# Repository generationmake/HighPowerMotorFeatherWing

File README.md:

# HighPowerMotorFeatherWing
HighPowerMotorFeatherWing with Infineon IFX007T drivers for two DC motors, up to 40V and 55A, compatible to Adafruit Feather

## PCB

### Top

### Bottom

## License

This hardware is licensed under the CERN OHL v. 1.2

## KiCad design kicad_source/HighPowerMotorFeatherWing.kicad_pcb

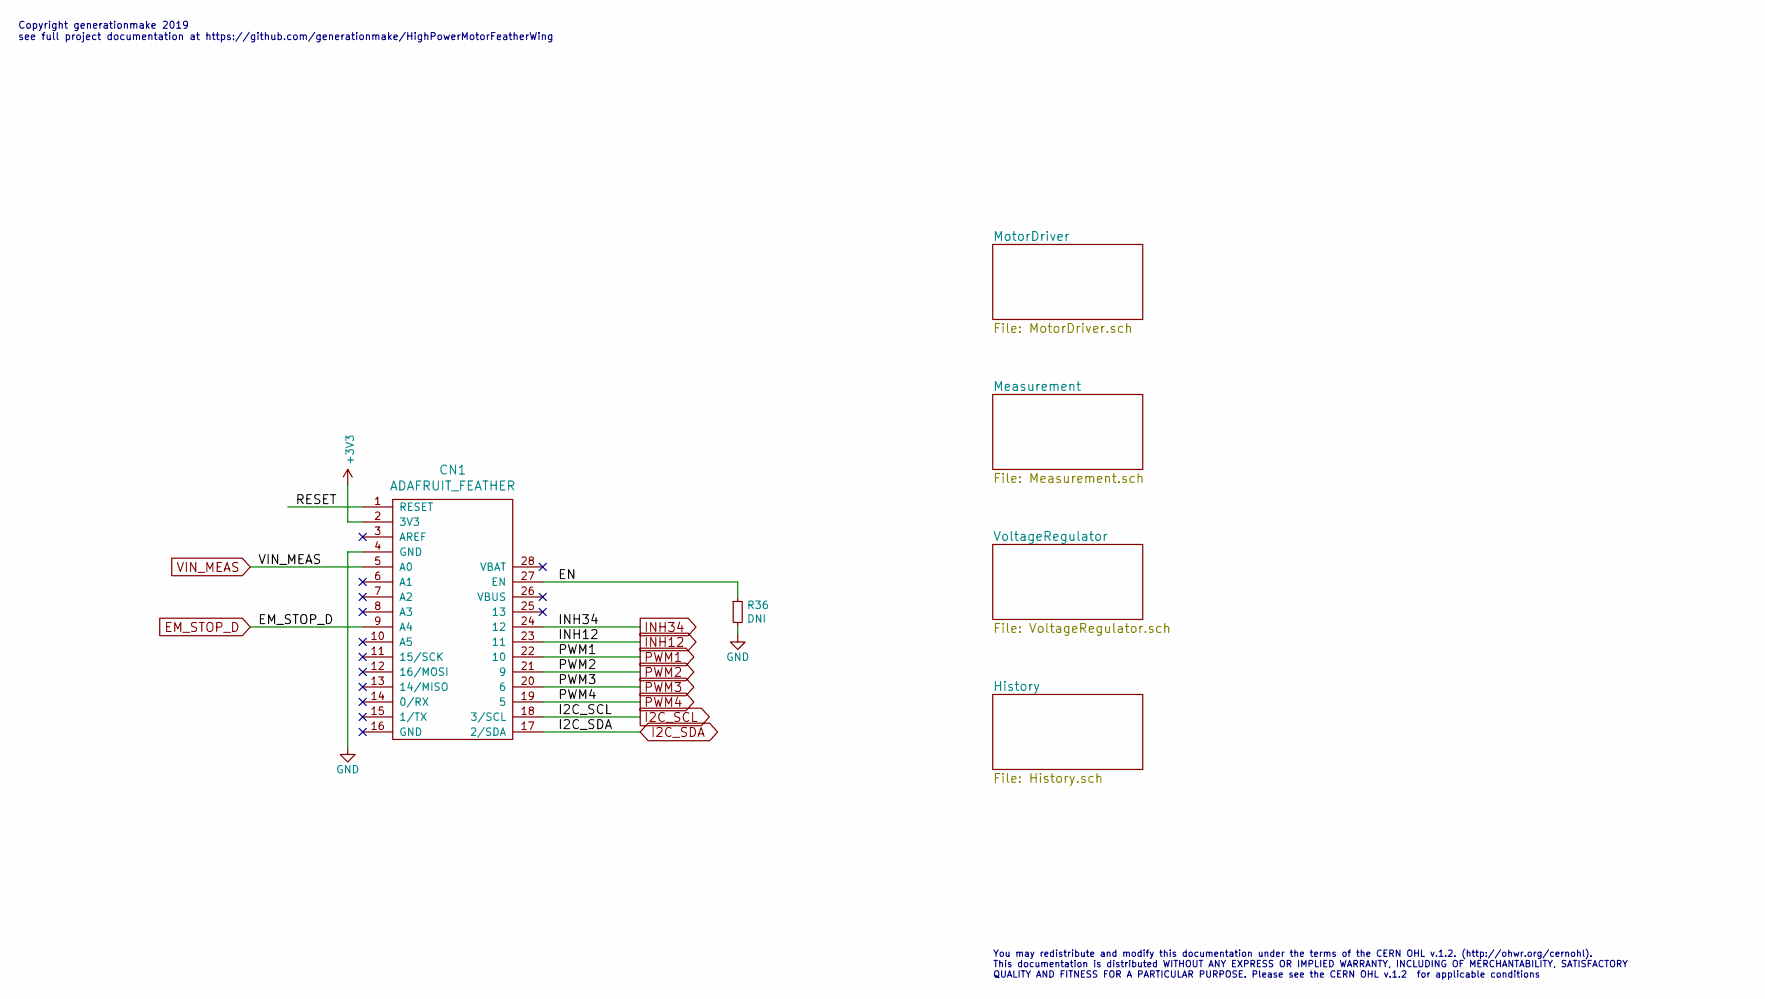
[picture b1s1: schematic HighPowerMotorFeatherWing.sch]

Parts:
CN1: ADAFRUIT_FEATHER; ADAFRUIT_FEATHER_HOLES
R36: DNI; R_0603

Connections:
+3V3: CN1.2 (3V3); also elsewhere on the board
/EN: CN1.27 (EN), R36.1
EM_STOP_D: CN1.9 (A4); also elsewhere on the board
GND: CN1.4 (GND), R36.2; also elsewhere on the board
I2C_SCL: CN1.18 (3/SCL); also elsewhere on the board
I2C_SDA: CN1.17 (2/SDA); also elsewhere on the board
INH12: CN1.23 (11); also elsewhere on the board
INH34: CN1.24 (12); also elsewhere on the board
PWM1: CN1.22 (10); also elsewhere on the board
PWM2: CN1.21 (9); also elsewhere on the board
PWM3: CN1.20 (6); also elsewhere on the board
PWM4: CN1.19 (5); also elsewhere on the board
VIN_MEAS: CN1.5 (A0); also elsewhere on the board

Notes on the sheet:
Copyright generationmake 2019 see full project documentation at https://github.com/generationmake/HighPowerMotorFeatherWing
You may redistribute and modify this documentation under the terms of the CERN OHL v.1.2. (http://ohwr.org/cernohl). This documentation is distributed WITHOUT ANY EXPRESS OR IMPLIED WARRANTY, INCLUDING OF MERCHANTABILITY, SATISFACTORY QUALITY AND FITNESS FOR A PARTICULAR PURPOSE. Please see the CER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

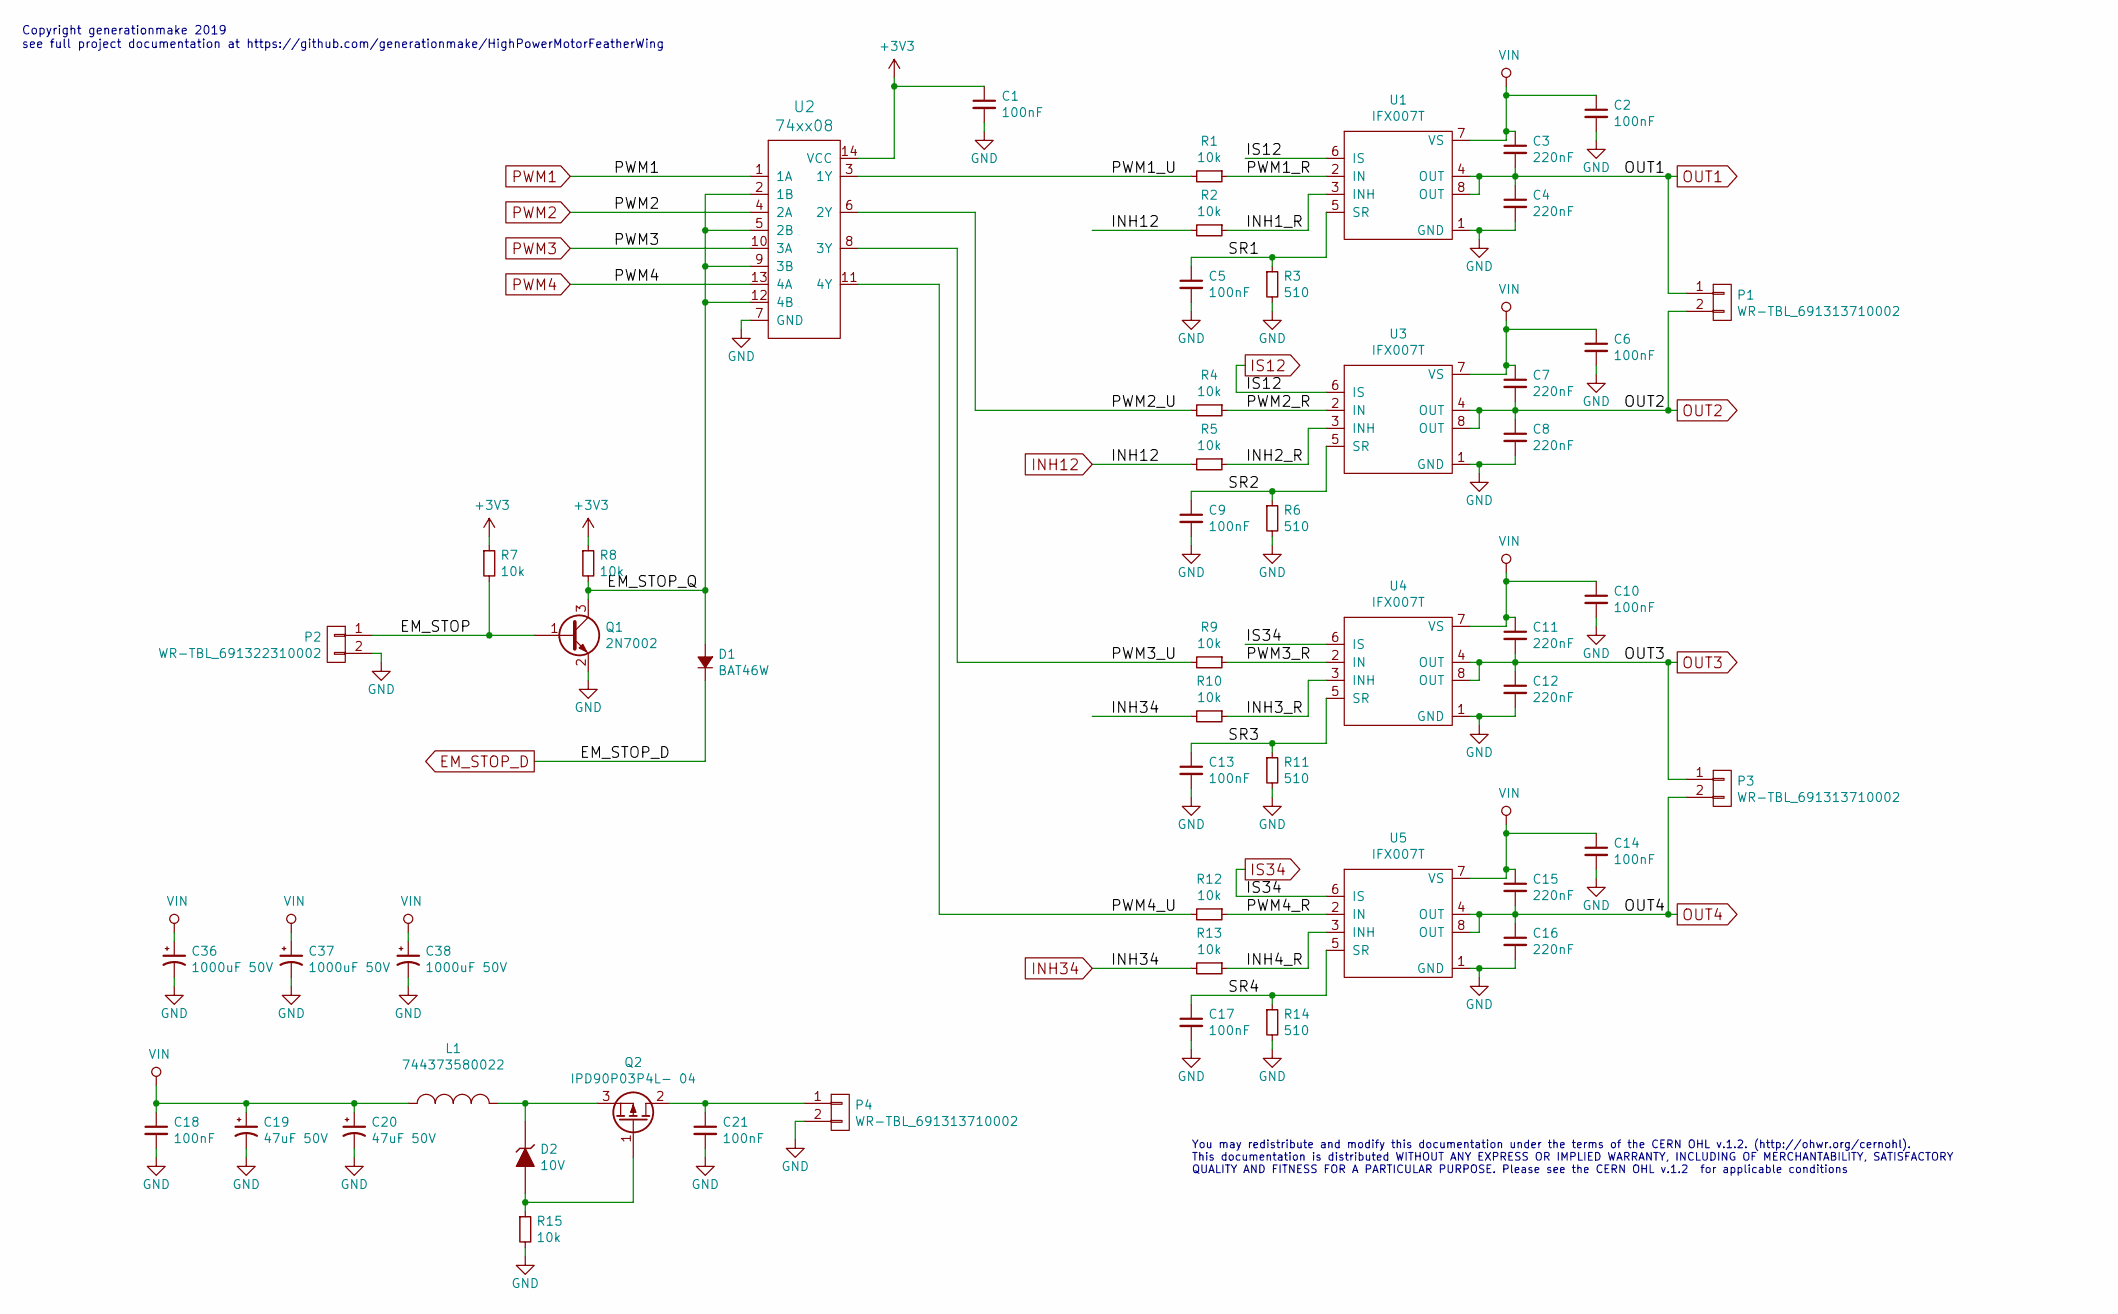
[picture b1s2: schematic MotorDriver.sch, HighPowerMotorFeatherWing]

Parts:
C1, C2, C5, C6, C9, C10, C13, C14, C17, C18, C21: 100nF; C_0603
C3, C4, C7, C8, C11, C12, C15, C16: 220nF; C_0603
C19, C20: 47uF 50V; TantalC_SizeD_EIA-7343_Wave
C36, C37, C38: 1000uF 50V; C_elec_THT_16x25_RM7.5
D1: BAT46W; SOD-123
D2: 10V; SOD-123
L1: 744373580022; WE-LHMI80xx
P1, P3, P4: WR-TBL_691313710002
P2: WR-TBL_691322310002
Q1: 2N7002; SOT-23
Q2: IPD90P03P4L- 04; TO-252-2Lead
R1, R2, R4, R5, R7, R8, R9, R10, R12, R13, R15: 10k; R_0603
R3, R6, R11, R14: 510; R_0603
U1, U3, U4, U5: IFX007T; TO-263-7Lead
U2: 74xx08; SOIC-14_3.9x8.7mm_Pitch1.27mm

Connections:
+3V3: C1.1, R7.1, R8.1, U2.14 (VCC); also elsewhere on the board
/MotorDriver/EM_STOP: P2.1, Q1.1 (B), R7.2
/MotorDriver/EM_STOP_Q: D1.2 (A), Q1.3 (C), R8.2, U2.2 (1B), U2.5 (2B), U2.9 (3B), U2.12 (4B)
/MotorDriver/INH1_R: R2.1, U1.3 (INH)
/MotorDriver/INH2_R: R5.1, U3.3 (INH)
/MotorDriver/INH3_R: R10.1, U4.3 (INH)
/MotorDriver/INH4_R: R13.1, U5.3 (INH)
/MotorDriver/PWM1_R: R1.1, U1.2 (IN)
/MotorDriver/PWM1_U: R1.2, U2.3 (1Y)
/MotorDriver/PWM2_R: R4.1, U3.2 (IN)
/MotorDriver/PWM2_U: R4.2, U2.6 (2Y)
/MotorDriver/PWM3_R: R9.1, U4.2 (IN)
/MotorDriver/PWM3_U: R9.2, U2.8 (3Y)
/MotorDriver/PWM4_R: R12.1, U5.2 (IN)
/MotorDriver/PWM4_U: R12.2, U2.11 (4Y)
/MotorDriver/SR1: C5.1, R3.1, U1.5 (SR)
/MotorDriver/SR2: C9.1, R6.1, U3.5 (SR)
/MotorDriver/SR3: C13.1, R11.1, U4.5 (SR)
/MotorDriver/SR4: C17.1, R14.1, U5.5 (SR)
EM_STOP_D: D1.1 (K); also elsewhere on the board
GND: C1.2, C2.2, C4.2, C5.2, C6.2, C8.2, C9.2, C10.2, C12.2, C13.2, C14.2, C16.2, C17.2, C18.2, C19.2, C20.2, C21.2, C36.2, C37.2, C38.2, P2.2, P4.2, Q1.2 (E), R3.2, R6.2, R11.2, R14.2, R15.2, U1.1 (GND), U2.7 (GND), U3.1 (GND), U4.1 (GND), U5.1 (GND); also elsewhere on the board
INH12: R2.2, R5.2; also elsewhere on the board
INH34: R10.2, R13.2; also elsewhere on the board
IS12: U1.6 (IS), U3.6 (IS); also elsewhere on the board
IS34: U4.6 (IS), U5.6 (IS); also elsewhere on the board
unnamed: C21.1, P4.1, Q2.2 (D)
unnamed: D2.1 (K), L1.2, Q2.3 (S)
unnamed: D2.2 (A), Q2.1 (G), R15.1
OUT1: C3.2, C4.1, P1.1, U1.4 (OUT), U1.8 (OUT); also elsewhere on the board
OUT2: C7.2, C8.1, P1.2, U3.4 (OUT), U3.8 (OUT); also elsewhere on the board
OUT3: C11.2, C12.1, P3.1, U4.4 (OUT), U4.8 (OUT); also elsewhere on the board
OUT4: C15.2, C16.1, P3.2, U5.4 (OUT), U5.8 (OUT); also elsewhere on the board
PWM1: U2.1 (1A); also elsewhere on the board
PWM2: U2.4 (2A); also elsewhere on the board
PWM3: U2.10 (3A); also elsewhere on the board
PWM4: U2.13 (4A); also elsewhere on the board
VIN: C2.1, C3.1, C6.1, C7.1, C10.1, C11.1, C14.1, C15.1, C18.1, C19.1, C20.1, C36.1, C37.1, C38.1, L1.1, U1.7 (VS), U3.7 (VS), U4.7 (VS), U5.7 (VS); also elsewhere on the board

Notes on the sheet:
Copyright generationmake 2019 see full project documentation at https://github.com/generationmake/HighPowerMotorFeatherWing
You may redistribute and modify this documentation under the terms of the CERN OHL v.1.2. (http://ohwr.org/cernohl). This documentation is distributed WITHOUT ANY EXPRESS OR IMPLIED WARRANTY, INCLUDING OF MERCHANTABILITY, SATISFACTORY QUALITY AND FITNESS FOR A PARTICULAR PURPOSE. Please see the CER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

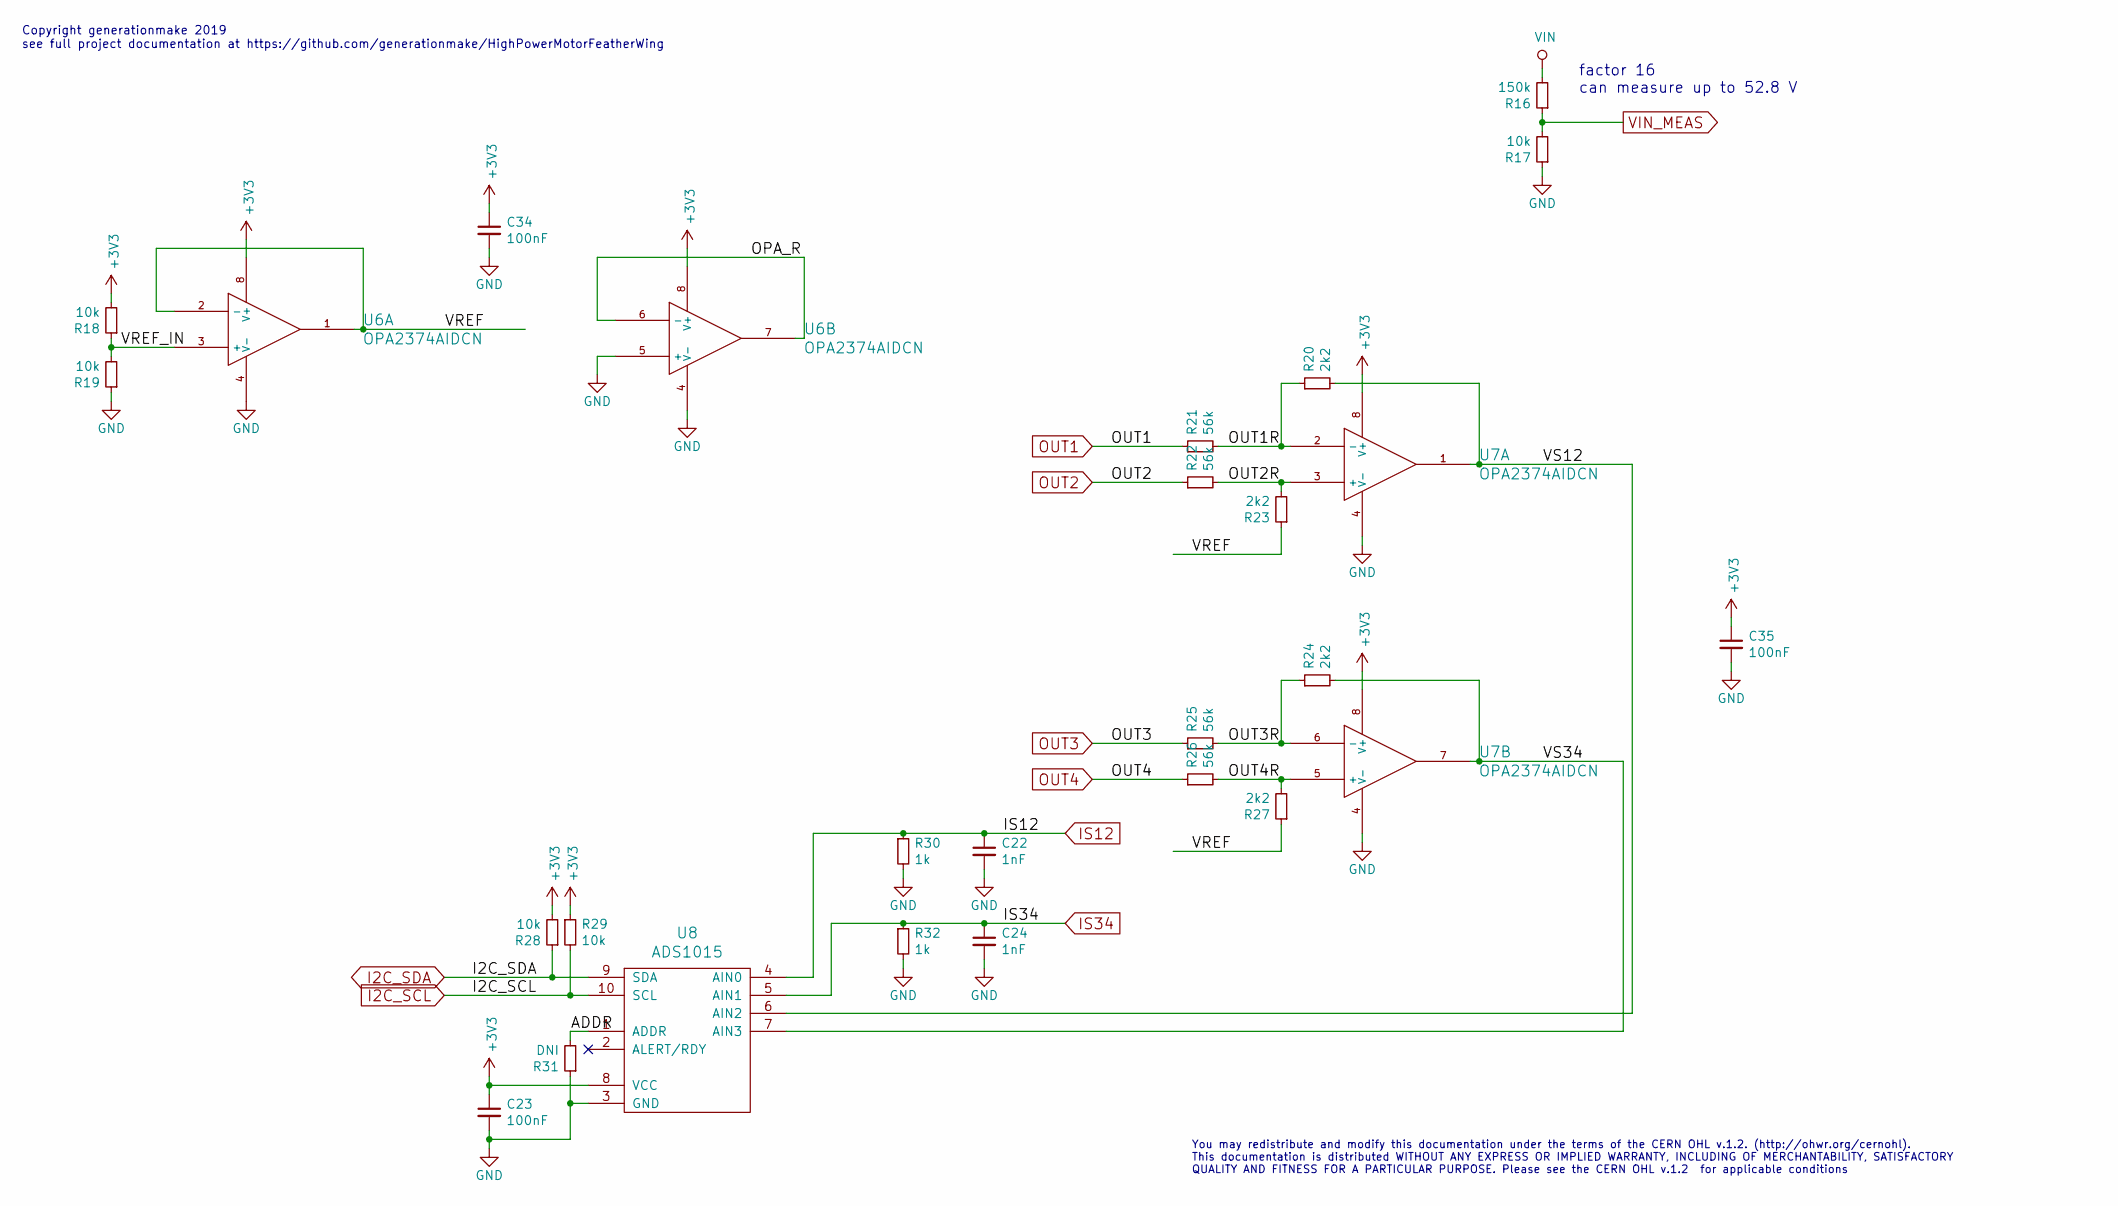
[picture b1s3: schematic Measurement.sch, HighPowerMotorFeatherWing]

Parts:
C22, C24: 1nF; C_0603
C23, C34, C35: 100nF; C_0603
R16: 150k; R_0603
R17, R18, R19, R28, R29: 10k; R_0603
R20, R23, R24, R27: 2k2; R_0603
R21, R22, R25, R26: 56k; R_0603
R30, R32: 1k; R_0603
R31: DNI; R_0603
U6, U7: OPA2374AIDCN; SOIC-8_3.9x4.9mm_Pitch1.27mm
U8: ADS1015; MSOP-10_3x3mm_Pitch0.5mm

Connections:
+3V3: C23.1, C34.1, C35.1, R18.2, R28.2, R29.1, U6.8 (V+), U7.8 (V+), U8.8 (VCC); also elsewhere on the board
/Measurement/ADDR: R31.2, U8.1 (ADDR)
/Measurement/OPA_R: U6.6 (-), U6.7
/Measurement/OUT1R: R20.1, R21.2, U7.2 (-)
/Measurement/OUT2R: R22.2, R23.2, U7.3 (+)
/Measurement/OUT3R: R24.1, R25.2, U7.6 (-)
/Measurement/OUT4R: R26.2, R27.2, U7.5 (+)
/Measurement/VREF: R23.1, R27.1, U6.1, U6.2 (-)
/Measurement/VREF_IN: R18.1, R19.2, U6.3 (+)
/Measurement/VS12: R20.2, U7.1, U8.6 (AIN2)
/Measurement/VS34: R24.2, U7.7, U8.7 (AIN3)
GND: C22.2, C23.2, C24.2, C34.2, C35.2, R17.1, R19.1, R30.2, R31.1, R32.2, U6.4 (V-), U6.5 (+), U7.4 (V-), U8.3 (GND); also elsewhere on the board
I2C_SCL: R29.2, U8.10 (SCL); also elsewhere on the board
I2C_SDA: R28.1, U8.9 (SDA); also elsewhere on the board
IS12: C22.1, R30.1, U8.4 (AIN0); also elsewhere on the board
IS34: C24.1, R32.1, U8.5 (AIN1); also elsewhere on the board
OUT1: R21.1; also elsewhere on the board
OUT2: R22.1; also elsewhere on the board
OUT3: R25.1; also elsewhere on the board
OUT4: R26.1; also elsewhere on the board
VIN: R16.2; also elsewhere on the board
VIN_MEAS: R16.1, R17.2; also elsewhere on the board

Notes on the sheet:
Copyright generationmake 2019 see full project documentation at https://github.com/generationmake/HighPowerMotorFeatherWing
You may redistribute and modify this documentation under the terms of the CERN OHL v.1.2. (http://ohwr.org/cernohl). This documentation is distributed WITHOUT ANY EXPRESS OR IMPLIED WARRANTY, INCLUDING OF MERCHANTABILITY, SATISFACTORY QUALITY AND FITNESS FOR A PARTICULAR PURPOSE. Please see the CER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
factor 16 can measure up to 52.8 V

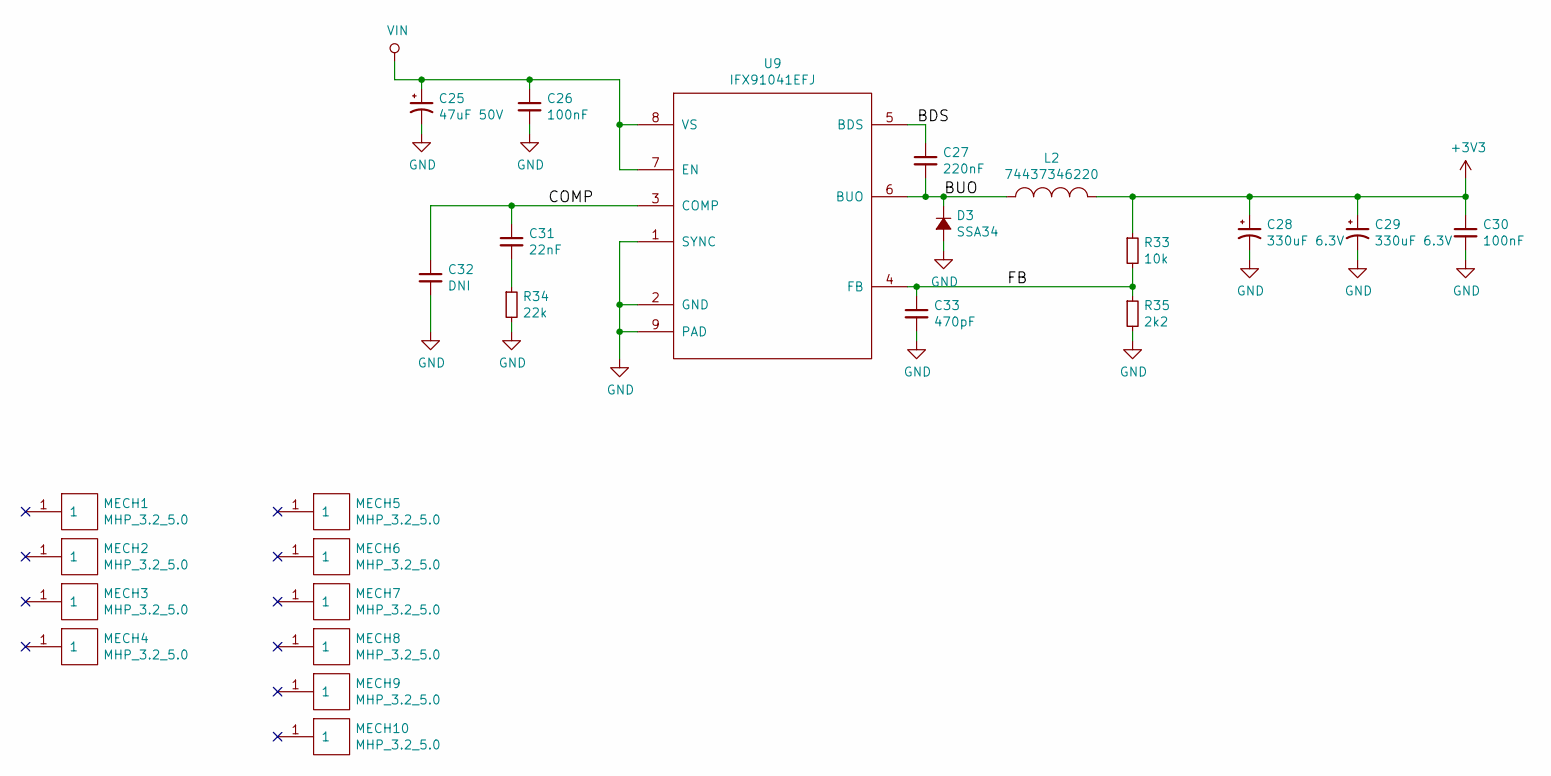
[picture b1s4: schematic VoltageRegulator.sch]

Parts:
C25: 47uF 50V; TantalC_SizeD_EIA-7343_Wave
C26, C30: 100nF; C_0603
C27: 220nF; C_0603
C28, C29: 330uF 6.3V; TantalC_SizeD_EIA-7343_Wave
C31: 22nF; C_0603
C32: DNI; C_0603
C33: 470pF; C_0603
D3: SSA34; SMA_Standard
L2: 74437346220; WE-LHMI70xx
MECH1, MECH2, MECH3, MECH4, MECH5, MECH6, MECH7, MECH8, MECH9, MECH10: MHP_3.2_5.0
R33: 10k; R_0603
R34: 22k; R_0603
R35: 2k2; R_0603
U9: IFX91041EFJ; SOIC-8-1EP_3.9x4.9mm_Pitch1.27mm

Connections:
+3V3: C28.1, C29.1, C30.1, L2.2, R33.1; also elsewhere on the board
/VoltageRegulator/BDS: C27.1, U9.5 (BDS)
/VoltageRegulator/BUO: C27.2, D3.1 (K), L2.1, U9.6 (BUO)
/VoltageRegulator/COMP: C31.1, C32.1, U9.3 (COMP)
/VoltageRegulator/FB: C33.1, R33.2, R35.1, U9.4 (FB)
GND: C25.2, C26.2, C28.2, C29.2, C30.2, C32.2, C33.2, D3.2 (A), R34.2, R35.2, U9.1 (SYNC), U9.2 (GND), U9.9 (PAD); also elsewhere on the board
unnamed: C31.2, R34.1
VIN: C25.1, C26.1, U9.7 (EN), U9.8 (VS); also elsewhere on the board

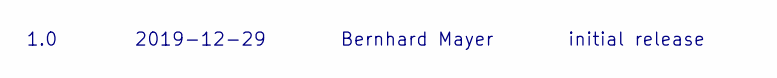
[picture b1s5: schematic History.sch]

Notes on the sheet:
1.0
2019-12-29
Bernhard Mayer
initial release

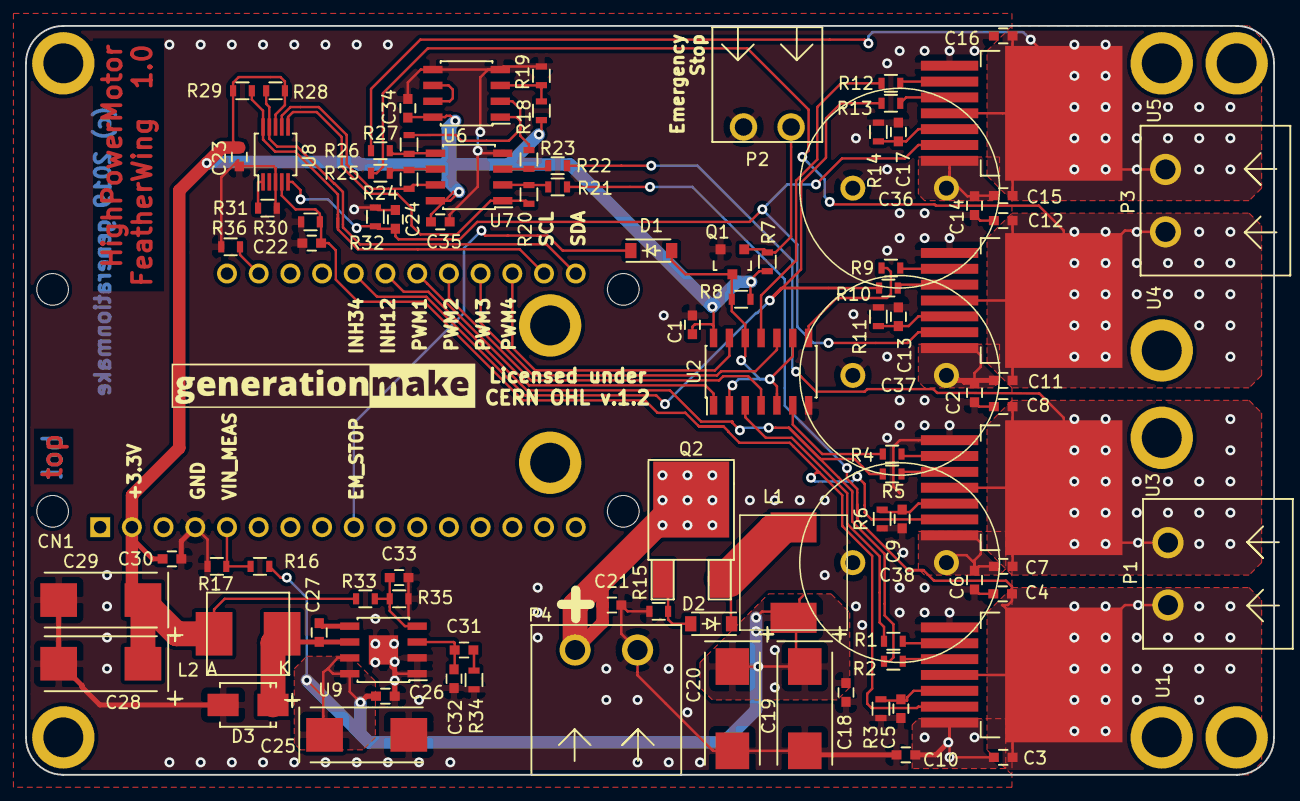
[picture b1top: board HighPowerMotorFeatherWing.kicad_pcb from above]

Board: 2 copper layers, 100.0 x 60.0 mm, 105 parts (0 on the bottom side), 56 nets.

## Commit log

2019-12-29 added kicad source
2019-12-29 added values in schematic, generated pdf schematic
2019-12-29 added manufacturing pdfs
2019-12-29 added license information
2019-12-30 added renderings, updated readme
2020-01-01 added mounting instructions
2020-01-29 added 3D model for Adafruit Feather connector
2020-04-16 changed mounting holes to parts and generated step file

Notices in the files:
kicad_source/HighPowerMotorFeatherWing.kicad_pcb:
(c) 2019 generationmake
This documentation describes Open Hardware and is licensed
under the CERN OHL v. 1.2.
kicad_source/HighPowerMotorFeatherWing.sch:
This documentation describes Open Hardware and is licensed under the CERN OHL v. 1.2.
